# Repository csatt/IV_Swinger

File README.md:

# IV_Swinger

**NOTICE: Please contact me at csatt1@gmail.com if you are interested in building the hardware for people who don't have the time, skills, or tools to do it themselves. I get requests occasionally from such people, but cannot do this myself. There are now PCBs, making the construction much easier!**

The IV Swinger is an IV curve tracer for photovoltaic solar panels. Both the hardware design and the software are open source.

This GitHub repository contains the IV Swinger documentation, software, and open source licensing files.

IV Swinger 2 is here! It is much smaller, cheaper and easier to build, and better than the original in almost every way. Step-by-step construction instructions are included in the repository, and are posted on www.instructables.com:

[IV Swinger 2 - a $50 IV Curve Tracer](http://www.instructables.com/id/IV-Swinger-2-a-50-IV-Curve-Tracer/)

All IV Swinger 2 documentation is now available:
* IV Swinger 2: User Guide
* IV Swinger 2: Optional Environmental Sensors
* IV Swinger 2: Hardware Scaling
* IV Swinger 2: Design and Theory of Operation
* IV Swinger 2: Step-by-step Construction (for each variant)
* Fritzing files
* PCB schematics
* Bills of materials (BOMs) for each variant

YouTube demo videos (IV Swinger 2):

YouTube demo video (original IV Swinger):

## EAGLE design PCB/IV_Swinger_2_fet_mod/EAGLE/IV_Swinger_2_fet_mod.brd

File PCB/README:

This folder contains subfolders for each different type of IV Swinger
PCB.  Each subfolder contains an EAGLE subfolder with the schematic and
board files created with the free version of EAGLE.  There is also a
Gerber subfolder with the manufacturing files (in a zip archive) and a
PDF subfolder with PDFs of the schematic and images of the top and
bottom of the PCB.

All PCBs are Arduino "shields" that replace the PermaProto board in the
original IV Swinger 2 design.  They plug onto the top of the Arduino.
All are 2-layer boards.

IV_Swinger_2_module
-------------------
  This is the version for PV modules that requires an external
  electromechanical relay (EMR) module, just like the original. The only
  external wiring is between one screw-terminal block on the PCB and the
  relay module and between another screw-terminal block and the binding
  posts.  Additional external wires are required for the optional
  temperature and irradiance sensors.

  RevB
  ----
  Based on RevB of the SSR-based module version. The main purpose of
  this revision is to make the SSR and EMR versions as similar as
  possible, namely:

     - the connections to the binding posts are both on a screw-terminal
       block on the left end of the board (like SSR version)

     - pads are provided for the bypass diodes (like SSR version)

     - the current-carrying path from the shunt is now isolated in a
       stub off the ground plane (like SSR version)

     - R3 is now connected to the shunt with a dedicated trace (like SSR
       version)

     - Connections to EMR are from a second screw-terminal block that is
       located on the board where the SSRs are in the SSR version

  Note that there is nothing "wrong", per se, with the RevA board. This
  just cleans a few things up and makes it much easier to compare it
  with the SSR version.
  
  Status:   Verified
  To order: Submit Gerber files to www.pcbway.com

  RevA
  ----
  Status: OBSOLETE (but bug-free)

IV_Swinger_2_cell
-----------------
  This is similar to the IV_Swinger_2_module Arduino shield, but it is
  for use with PV cells.

  RevA
  ----
  Status:   Verified
  To order: Submit Gerber files to www.pcbway.com

IV_Swinger_2_ss_mod
-------------------
  This is similar to the IV_Swinger_2_module Arduino shield, but it uses
  three solid-state relays (SSRs) instead of the one electromechanical
  relay (EMR) module.  The only off-board connections are to the PV
  module itself (PV- and PV+). These can go to binding posts, or can be
  connected directly to wires with MC-4 connectors on their ends.

  RevB
  ----
  Status: Verified

  To order: Submit Gerber files to www.pcbway.com

  RevA
  ----
  Status: OBSOLETE (bugs: Issue #40, Issue #41; not viable)

IV_Swinger_2_ss_cell
--------------------
  This is similar to the IV_Swinger_2_ss_mod Arduino shield, but it is
  for use with PV cells.  It requires four SSRs.

  RevB
  ----
  Status:   Verified
  To order: Submit Gerber files to www.pcbway.com

  RevA
  ----
  Status:   OBSOLETE (bug: Issue #49, rework possible)

--------------------------------------------------------------------------------

Advantages of EMR designs:
  - EMR module is inexpensive (~$2), vs three/four SSRs (~$21/$28)
  - "Clicks" tell you it's working
  - EMR module is easy to replace if it goes bad
  
Advantages of SSR designs:
  - On-board:
     - No wires
     - No relay module to mount
  - Rated at 100V
  - No mechanical wearout
  - Silent

NOTE: The IV Swinger 2 Arduino code and application software work with
      all four variants.

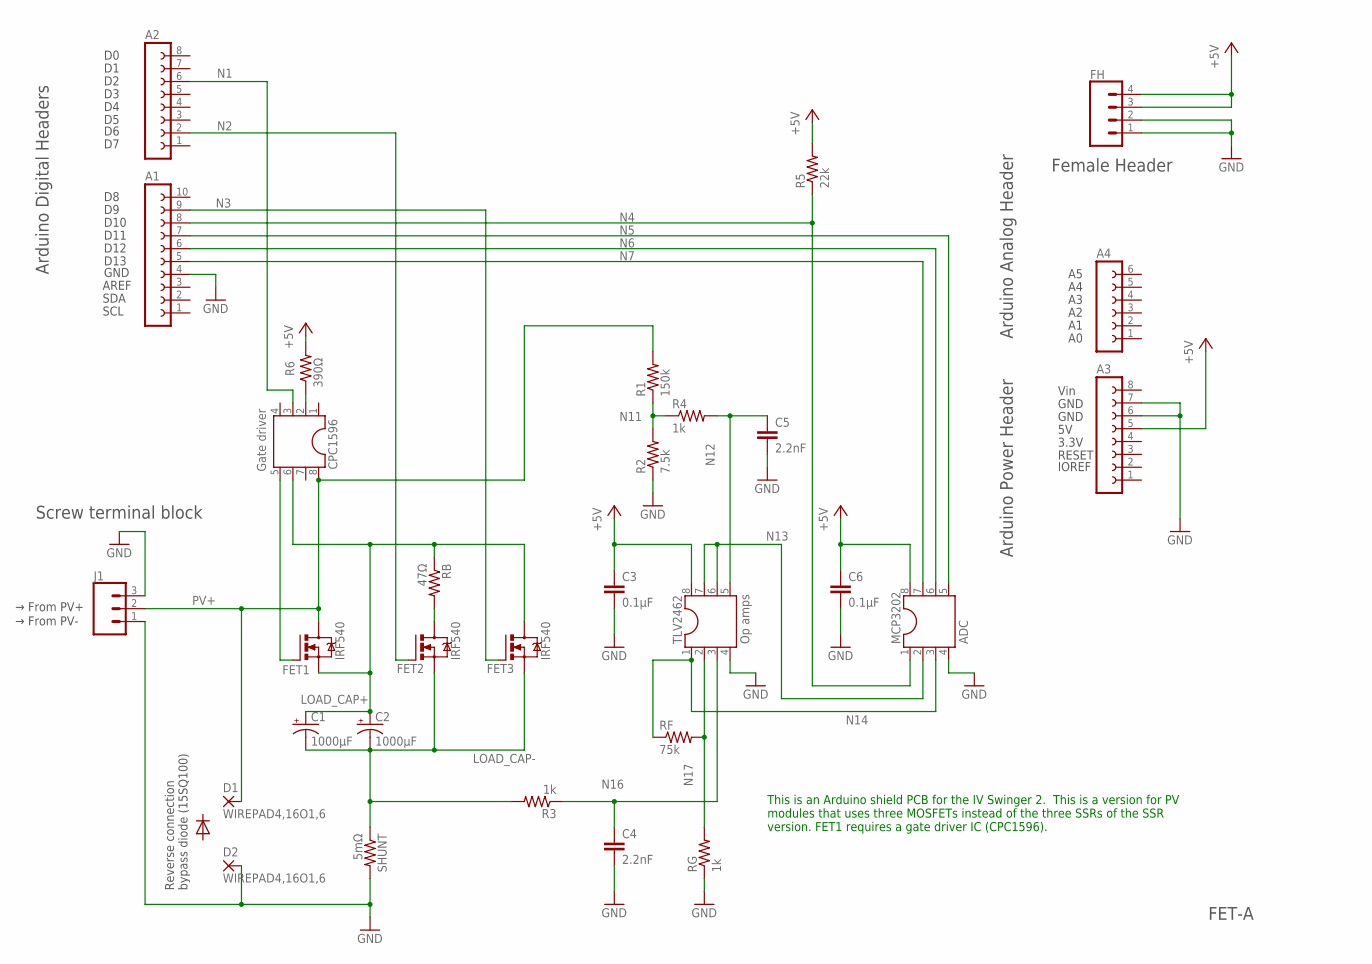
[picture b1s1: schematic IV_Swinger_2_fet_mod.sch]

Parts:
A1: FE10-1; FE10
A2, A3: FE08-1; FE08
A4: FE06-1; FE06
C1, C2: 1000µF; E7,5-18
C3, C6: 0.1µF; C025-030X050
C4, C5: 2.2nF; C025-030X050
CPC1596: Gate driver; SOCKET-08
D1, D2: WIREPAD4,16O1,6; 4,16O1,6
FET1, FET2, FET3: IRF540; TO220BV
FH: CONN_04LONGPADS; 1X04_LONGPADS
J1: SCREWTERMINAL-5MM-3
MCP3202: ADC; SOCKET-08
R1: 150k; 0207/10
R2: 7.5k; 0207/10
R3, R4: 1k; 0207/10
R5: 22k; 0207/10
R6: 390Ω; 0207/10
RB: 47Ω; P0817V
RF: 75k; 0207/10
RG: 1k; 0207/10
SHUNT: 5mΩ; 0617V
TLV2462: Op amps; SOCKET-08

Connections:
+5V: A3.5, C3.1, C6.1, FH.3, FH.4, MCP3202.8, R5.2, R6.2, TLV2462.8
GND: A1.4, A3.6, A3.7, C3.2, C4.2, C5.2, C6.2, D2.1, FH.1, FH.2, J1.1, J1.3, MCP3202.4, R2.1, RG.1, SHUNT.2, TLV2462.4
LOAD_CAP+: C1.+, C2.+, CPC1596.6, FET1.S, FET3.D, RB.1
LOAD_CAP-: C1.-, C2.-, FET2.S, FET3.S, R3.2, SHUNT.1
N1: A2.6, CPC1596.3
N2: A2.2, FET2.G
N3: A1.9, FET3.G
N4: A1.8, MCP3202.1, R5.1
N5: A1.7, MCP3202.5
N6: A1.6, MCP3202.6
N7: A1.5, MCP3202.7
N11: R1.1, R2.2, R4.1
N12: C5.1, R4.2, TLV2462.5
N13: MCP3202.2, TLV2462.6, TLV2462.7
N14: MCP3202.3, RF.1, TLV2462.1
N16: C4.1, R3.1, TLV2462.3
N17: RF.2, RG.2, TLV2462.2
unnamed: FET2.D, RB.2
unnamed: CPC1596.5, FET1.G
unnamed: CPC1596.2, R6.1
PV+: CPC1596.8, D1.1, FET1.D, J1.2, R1.2

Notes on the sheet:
→ From PV-
Screw terminal block
SCL
SDA
AREF
D13
D12
GND
D10
D11
RESET
3.3V
IOREF
Vin
Arduino Digital Headers
Arduino Analog Header
Arduino Power Header
Female Header
FET-A
This is an Arduino shield PCB for the IV Swinger 2. This is a version for PV modules that uses three MOSFETs instead of the three SSRs of the SSR version. FET1 requires a gate driver IC (CPC1596).
→ From PV+
Reverse connection bypass diode (15SQ100)

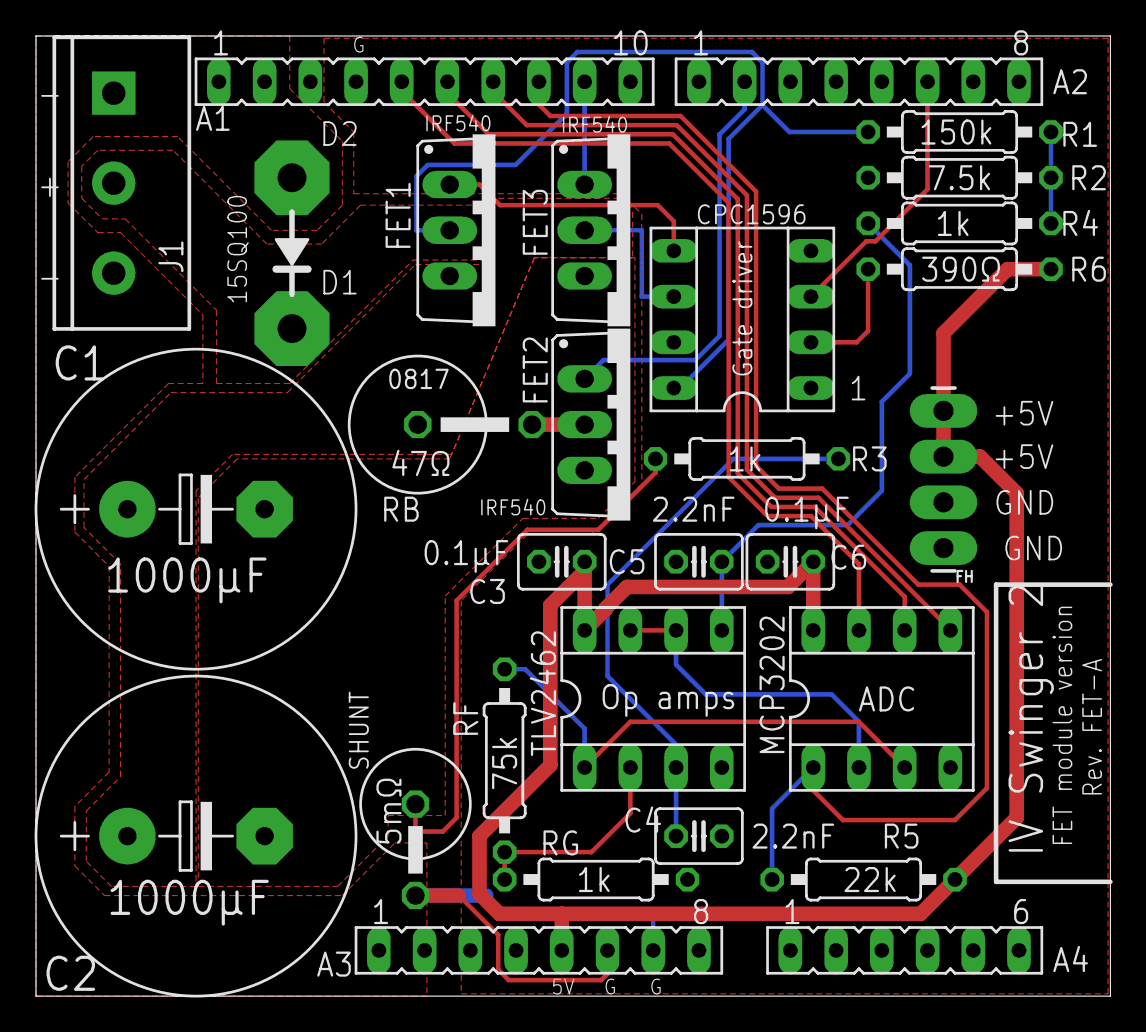
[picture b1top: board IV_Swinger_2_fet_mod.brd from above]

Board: 2 copper layers, 59.7 x 53.3 mm, 30 parts (0 on the bottom side), 21 nets.

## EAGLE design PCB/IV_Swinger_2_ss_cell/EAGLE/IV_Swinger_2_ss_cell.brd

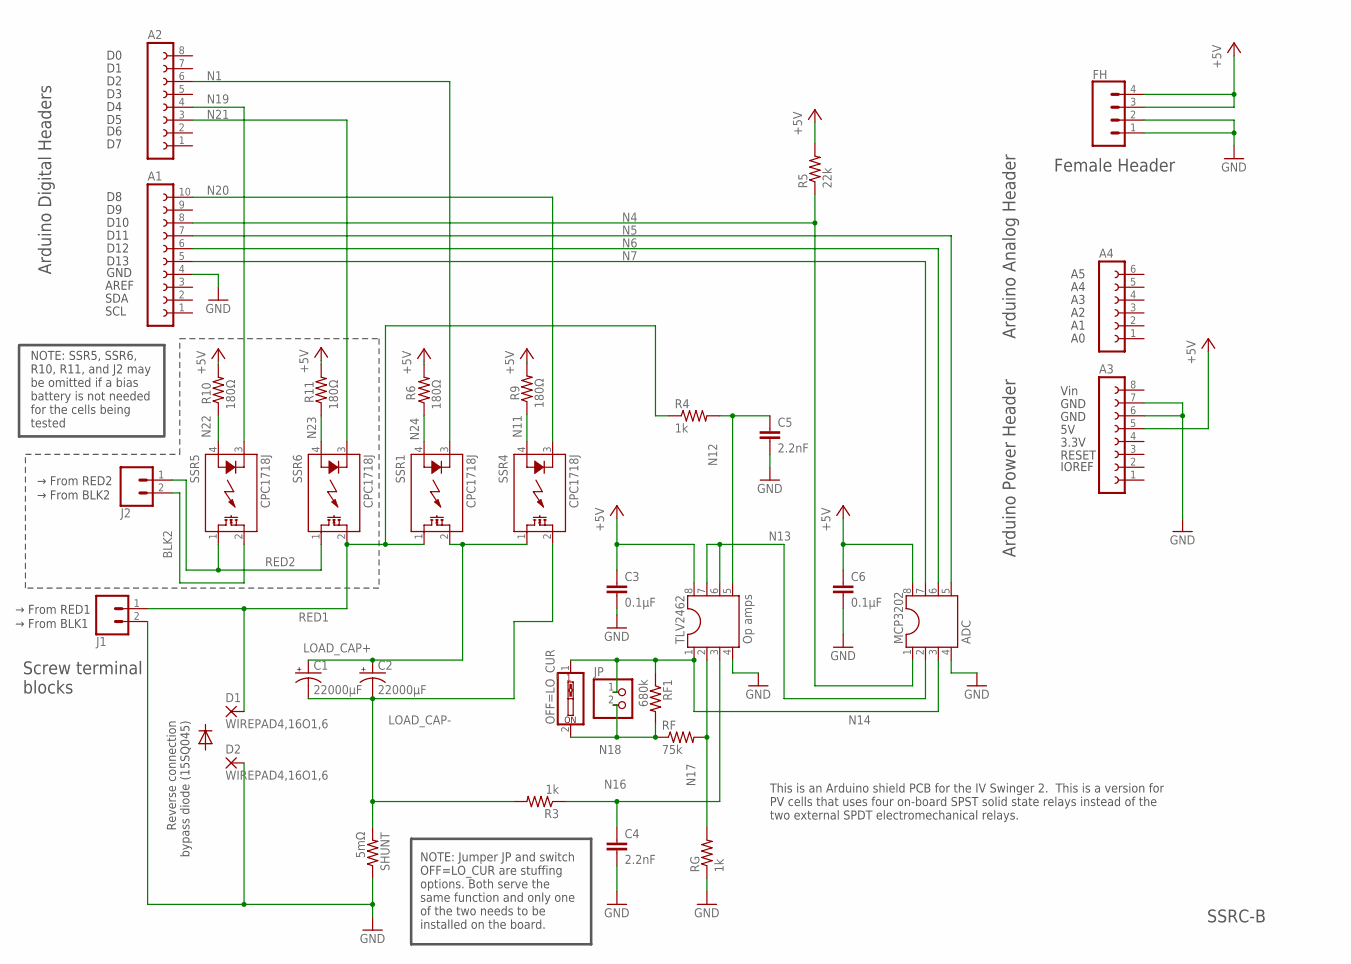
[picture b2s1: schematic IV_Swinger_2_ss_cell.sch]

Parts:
A1: FE10-1; FE10
A2, A3: FE08-1; FE08
A4: FE06-1; FE06
C1, C2: 22000µF; E7,5-18
C3, C6: 0.1µF; C025-030X050
C4, C5: 2.2nF; C025-030X050
D1, D2: WIREPAD4,16O1,6; 4,16O1,6
FH: CONN_04LONGPADS; 1X04_LONGPADS
J1, J2: CONN_025MM; SCREWTERMINAL-5MM-2
JP: PINHD-1X2; 1X02
MCP3202: ADC; SOCKET-08
OFF=LO_CUR: SW_DIP-1; EDG-01
R3, R4: 1k; 0207/10
R5: 22k; 0207/10
R6, R9, R10, R11: 180Ω; 0207/10
RF: 75k; 0207/10
RF1: 680k; 0207/10
RG: 1k; 0207/10
SHUNT: 5mΩ; 0617/17
SSR1, SSR4, SSR5, SSR6: CPC1718J; I4-PAC
TLV2462: Op amps; SOCKET-08

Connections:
+5V: A3.5, C3.1, C6.1, FH.3, FH.4, MCP3202.8, R5.2, R6.2, R9.2, R10.2, R11.2, TLV2462.8
BLK2: J2.2, SSR5.2 (DS2)
GND: A1.4, A3.6, A3.7, C3.2, C4.2, C5.2, C6.2, D2.1, FH.1, FH.2, J1.2, MCP3202.4, RG.1, SHUNT.1, TLV2462.4
LOAD_CAP+: C1.+, C2.+, SSR1.2 (DS2), SSR4.1 (DS1)
LOAD_CAP-: C1.-, C2.-, R3.2, SHUNT.2, SSR4.2 (DS2)
N1: A2.6, SSR1.3 (K)
N4: A1.8, MCP3202.1, R5.1
N5: A1.7, MCP3202.5
N6: A1.6, MCP3202.6
N7: A1.5, MCP3202.7
N11: R9.1, SSR4.4 (A)
N12: C5.1, R4.2, TLV2462.5
N13: MCP3202.2, TLV2462.6, TLV2462.7
N14: JP.1, MCP3202.3, OFF=LO_CUR.1, RF1.1, TLV2462.1
N16: C4.1, R3.1, TLV2462.3
N17: RF.2, RG.2, TLV2462.2
N18: JP.2, OFF=LO_CUR.2, RF.1, RF1.2
N19: A2.4, SSR5.3 (K)
N20: A1.10, SSR4.3 (K)
N21: A2.3, SSR6.3 (K)
N22: R10.1, SSR5.4 (A)
N23: R11.1, SSR6.4 (A)
N24: R6.1, SSR1.4 (A)
RED1: D1.1, J1.1, R4.1, SSR1.1 (DS1), SSR6.2 (DS2)
RED2: J2.1, SSR5.1 (DS1), SSR6.1 (DS1)

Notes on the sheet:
→ From BLK1
Screw terminal blocks
SCL
SDA
AREF
D13
D12
GND
D10
D11
RESET
3.3V
IOREF
Vin
Arduino Digital Headers
Arduino Analog Header
Arduino Power Header
Female Header
SSRC-B
This is an Arduino shield PCB for the IV Swinger 2. This is a version for PV cells that uses four on-board SPST solid state relays instead of the two external SPDT electromechanical relays.
→ From RED1
→ From BLK2
→ From RED2
NOTE: Jumper JP and switch OFF=LO_CUR are stuffing options. Both serve the same function and only one of the two needs to be installed on the board.
NOTE: SSR5, SSR6, R10, R11, and J2 may be omitted if a bias battery is not needed for the cells being tested
Reverse connection bypass diode (15SQ045)

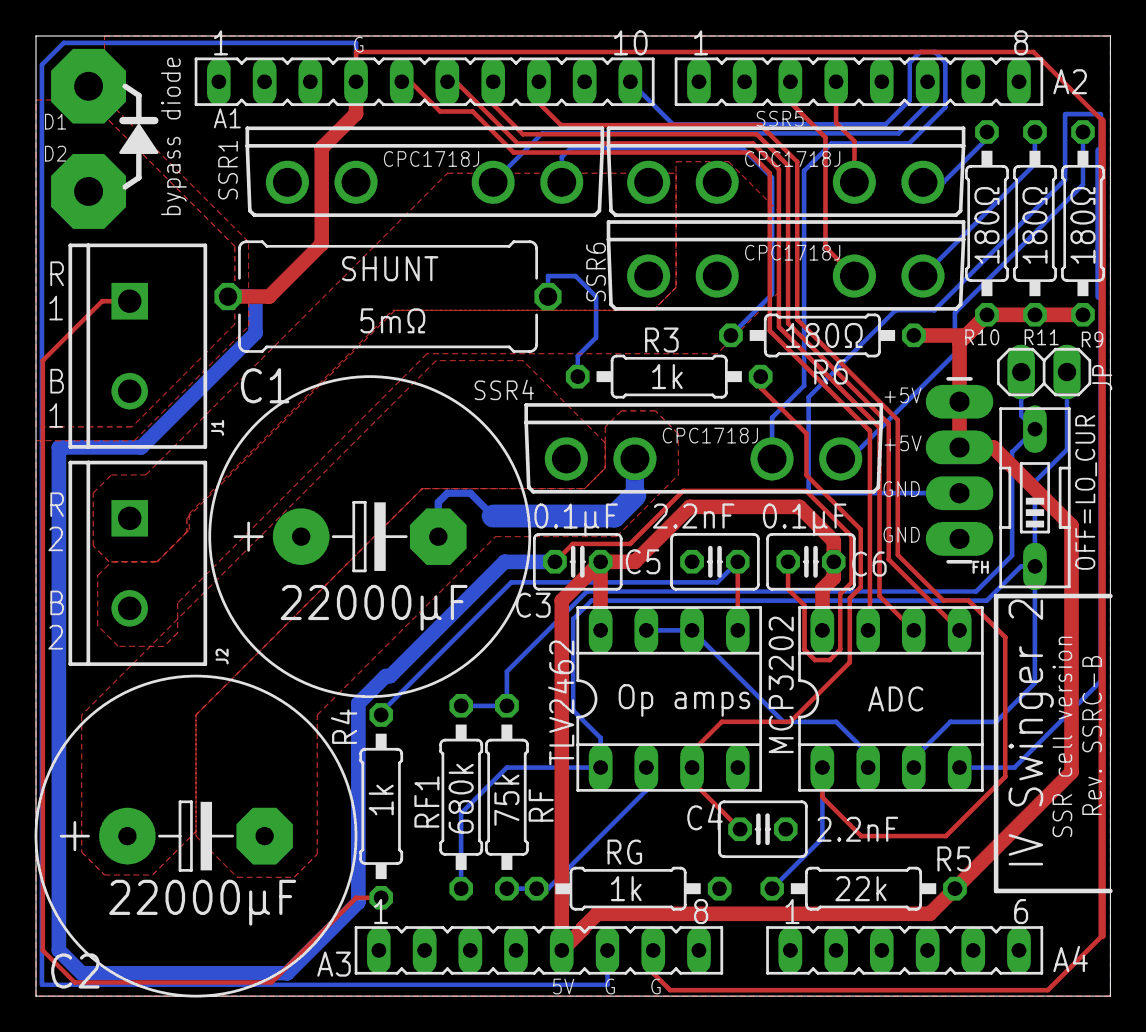
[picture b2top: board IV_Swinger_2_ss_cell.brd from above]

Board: 2 copper layers, 59.7 x 53.3 mm, 34 parts (0 on the bottom side), 25 nets.

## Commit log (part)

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2019-05-21 Fix handling of non-ASCII characters (Issue #66)
    The list of serial ports is obtained from serial.tools.list_ports.comports(). Each member of this list is an object of class serial.tools.list_ports.ListPortInfo. That class has a __str__ method that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
    The fix is to not use str(serial_port), but to use serial_port.device and serial_port.description and use them as unicode. It turns out that serial_port.manufacturer is useful too.
    The code caus
2019-10-11 Remove code to handle cycling noise floor (Issue #70)
    Remove the unnecessary and confusing code to handle noise floor cycling. See Issue #70.
2019-10-13 Fix spelling errors / typos
    This is one of the many cosmetic problems reported by Issue #74.
2019-10-13 Enhance error message to include bad return code (Issue #74)
    Add bad return codes to a couple error messages.
    This is one of the many minor problems reported by Issue #74.
2019-10-14 Log USB disconnection (Issue #77)
    Log warning message when the USB port has been determined to be disconnected by the usb_port_disconnected() method.
2019-10-14 Allow negative advanced calibration intercept values (Issue #85)
    Change the checking in the update_intercept() method to allow values between -0.5 and 0.5 (previously was between 0.0 and 0.5).
2019-10-15 Fix pylint "fixme" (Issue #87)
    Removed the "FIXME" from the comment. Workaound is permanent and there are no plans to determine the root cause.
2019-10-30 Fix pylint "no-member" (Issue #87)
    This one found two real bugs!
    This check has to be disabled for the windows-specific line that it complains about.
2019-10-31 Fix pylint "redefined-builtin" (Issue #87)
    Changed names of variables, "file", "str", "dir" and "id" to not conflict with the built-in names.
2019-11-01 Fix pylint "wrong-import-order" (Issue #87)
    Made changes to import order as recommended by pylint
2019-11-01 Fix pylint "too-many-ancestors" (Issue #87)
    All of these are disabled. The complaints are all about classes that extend a ttk class. There's not much that can be done if the library class has too many ancestors for pylint's liking. It could be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
2019-11-01 Fix pylint "too-many-statements" (Issue #87)
    Again, all legitimate, but disabled.
2019-12-06 Fix exception (Issue #94)
    Move the line that sets v_cal_b before the if statement so it gets initialized even if battery_bias is True.
2019-12-10 Update design doc
    Very minor changes to the software section to sync with code changes.
2020-06-27 Add font control and unicode title supoprt (Issue #105)
    Added "font name" to "Plotting" configuration. Added font_name property. Added --font_name option to plotter. Fixed titles to support unicode. Added widgets to Plotting tab of Preferences to set font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
2020-07-17 GitHub glitch?
    Very strange. After the previous commit, there was one line in IV_Swinger2.py still differing. Committing that now.
2020-07-26 Update version to v2.6.0
    Update from v2.5.2 to v2.6.0
2020-09-13 Change most xrange() to range()
    Except for one case in IV_Swinger2_sim.py, xrange() is used for reasonably small ranges and provides no benefits over range(). Since Python 3 has no xrange() function, all but that one xrange() are c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
2020-10-14 Create python3 directory and copy files (Issue #121)
    This is step 0 of the port to Python 3:
    - python3 directory is created
    - Files are copied, unchanged, from python directory
    To be clear, the code is still Python 2. But using this as a starting point will make it easier to see the diffs in the Python 3 code.
2020-10-14 Open all files with UTF-8 encoding (Issue #121)
    Surprisingly, Python 3 does not open all text files with UTF-8 encoding by default. To assure that all files are opened with UTF-8 encoding, the encoding="utf-8" option is added to all file open() co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
2020-10-16 Add support for Python 3 to mac_run_pyi
    The mac_run_pyi script now requires either "python" or "python3" as an argument to determine whether to build the Python 2 or Python 3 code.
2020-10-29 Fix pylint R1722 (Issue #124)
    R1722: Consider using sys.exit() (consider-using-sys-exit)
    Replaced all instances of exit(-1) with sys.exit(-1) in IV_Swinger.py and IV_Swinger_plotter.py (both python and python3).
    See https://www.geeksforgeeks.org/python-exit-commands-quit-exit-sys-exit-and-os-_exit/ for reason why sys.exit() is preferred.
2020-10-30 Fix pylint R0901 (Issue #124)
    IV_Swinger2_gui.py:4300:0: R0901: Too many ancestors (8/7) (too-many-ancestors)
    Disabled in both python and python3.
2020-10-31 Include simulation logging in main log file (Issue #126)
    To fix this, the following changes were made:
    - Add optional logger parameter to the IV_Swinger2 class initializer
    - Add logger parameter to IV_Swinger2 configure logging method
    - Modify configure_logging to just set the logger attribute to the passed value if it is set
    - Add optional logger parameter to the IV_Swinger2_sim class initializer and pass that to the IV_Swinger2 initializer
    - Add optional logger parameter to the SimulatorDialog class initializer and pass that to the IV_Swinger2_sim instantiation
2020-11-04 Fix double title in log file dialog (Mac)
    No Issue filed. The title in the log file dialog is repeated when the Python 2 code is run with 2.7.18 or when the Python 3 code is run (Mac only). It is not duplicated when the Python 2 code is run 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
    In any case, the solution is to not set both the "title" and "message" option for tkfiledialog.askopenfilename(), but rather set only the "message" option if the code is running on Mac.
    For some reason, this doesn't seem to be necessary for tkfiledialog.askdirectory(), which is used in get_copy_dest() and change_folder(). For consistenc
2020-11-07 Add Control-click to tooltip and help text (Issue #134)
    Changed all instances of "Control-click" to "Control-click (or Command-click)" in Results Wizard tooltip and help dialog text.
2020-11-12 Fixed typo in advanced calibration help
    No Issue filed. Added missing word. "it".
2020-11-15 Fix pylint C1614
    No Issue filed. Fix pylint complaint about bad continuation. The python3 version did not have this issue, but the formatting of the analogous lines is changed too in order to minimize the diffs betwe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
2020-11-30 Set matplotlib font type to TrueType (Issue #152)
    Per: http://phyletica.org/matplotlib-fonts/
    Added:
    matplotlib.rcParams['pdf.fonttype'] = 42 # TrueType
2020-12-04 Capture assert message in plot_results (Issue #158)
    The assertion message is captured in an IV_Swinger2 property so the GUI code can display it in the error dialog.
2020-12-11 Change to SSR calibration algorithm (Issue #163)
    Modify the previous fix for Issue #163.
    - The criterion for excluding Pass 2 values is changed. Now values that are within +/- 1 ADC count of the Pass 1 average are not excluded even if this means they differ by more than 0.5% from that av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
    - The criterion for determining if the measurement is stable is changed. Now the measurement is considered stable if the majority of Pass 2 values are not excluded. Previously, the measurement could 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
2020-12-20 Fix clean_up_after_failure() method (Issue #165)
    Instead of inferring that run_dir contains the ADC and data points CSV files if it contains two files, explcitly check that it indeed contains those two files.
2021-01-08 Move plot_and_view_modeled_curve() into main() (Issue #172)
    The plot_and_view_modeled_curve() function is moved into main() as a local function. This makes the "boilerplate" main() call much closer to being boilerplate. It still has the import of IV_Swinger2.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
2021-07-01 Fix equation for plot_ref_failed (Issue #175)
    In the equation for plot_ref_failed, qualify the condition where the CSV file name is None with the return code also being RC_SUCCESS.
2022-01-27 Update IV_Swinger2_FET_mod_PCB_Step_by_Step.docx
    File had not been saved in Word in previous commit. Very minor diffs.
2022-02-28 Update files for SSR cell Instructable
    Updated the step-by-step doc and BOMs for the SSR cell version. Mostly add alternate parts.
    Note that the Instructable itself has not bee created and probably never will be.
2022-12-26 Add READ_ADC command for debug with serial monitor (Issue #184)
    Added a new "config" (misnomer in this case) command to simply read both channels of the ADC and print their values. It has a count parameter that specifies the number of times to repeat the reads in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
2023-01-21 Fix pylint warnings in Tooltip.py (Issue #187)
    Fix the following:
    ************* Module Tooltip
    Tooltip.py:2:0: R0402: Use 'from tkinter import ttk' instead (consider-using-from-import)
    Tooltip.py:119:12: R1731: Consider using 'x_delta = max(x_delta, 0)' instead of unnecessary if block (consider-using-max-builtin)
    Tooltip.py:122:12: R1731: Consider using 'y_delta = max(y_delta, 0)' instead of unnecessary if block (consider-using-max-builtin)
2023-03-12 Add support for instances (Issue #192)
    This commit adds the feature requested in Issue #192.
    IV_Swinger2_gui.py
    - GraphicalUserInterface class changes:
    - __init__:
    - Add instance and main_gui creation parameters
    - Add attributes:
2023-04-05 Catch exception for port in use (Issue #197)
    Added try/except for call to zmq_socket.bind. Display error dialog if caught.
    Also in __init__, start remote_monitor() with after_idle so exceptions will be handled normally rather than with handle_early_exception().
2023-04-07 Another update to build_tools README
    Removed the pyinstaller workaround for the msgcat bug since it is no longer necessary
2023-04-09 Include inst path in copy destination (Issue #203)
    Modify the get_dest_dir() method to insert the "inst/<name>" part of the source path in the destination path, if it exists.
    Take advantage of the fact that os.path.join inserts directory separators only for non-empty segments. By initializing inst_path and overlays to "", this avoids multiple branches and should have been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
2023-04-14 Remove version from doc PDF names
    Remove version number from document PDF file names. This keeps links from breaking when the file is updated.
2023-06-13 Replace os.remove(x) with Path(x).unlink() (Issue #210)
    This is an incremental change. For now, all instances of os.remove(x) are replaced with Path(x).unlink().
    Later, all the "x" paths will themselves be changed from strings to Path objects, and these will all be changed from Path(x).unlink(x) to simply x.unlink().
2023-06-30 Convert run_info_filename and others to Path (Issue #210)
    This is another incremental change to refactor the code to use pathlib Path objects.
    The following are converted:
    sensor_info_filename
    run_info_filename
    cfg_filename
    starting_cfg_filename
2023-07-26 Next incremental batch of pathlib changes (Issue #210)
    This one mostly converts calls to open() to calls to the open() method or the Path object. However, some are replaced by calls to the read_text(), write_text(), or touch() methods.
2023-07-28 Fix refurb FURB124 suggestions (Issue #215)
    Fixed these:
    csatt@Chriss-2021-MBP_209.16:49:19[GitHub/IV_Swinger/python3]=> refurb --disable-all --enable FURB124 *.py
    IV_Swinger2_gui.py:3198:12 [FURB124]: Replace `x is y and z is y` with `x is y is z`
    IV_Swinger2_gui.py:3910:16 [FURB124]: Replace `x is y and z is y` with `x is y is z`
    IV_Swinger2_gui.py:9661:16 [FURB124]: Replace `x == y and z == y` with `x == y == z`

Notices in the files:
parts and their libraries:
SparkFun-Connectors: Licensing: Creative Commons ShareAlike 4.0 International - https://creativecommons.org/licenses/by-sa/4.0
